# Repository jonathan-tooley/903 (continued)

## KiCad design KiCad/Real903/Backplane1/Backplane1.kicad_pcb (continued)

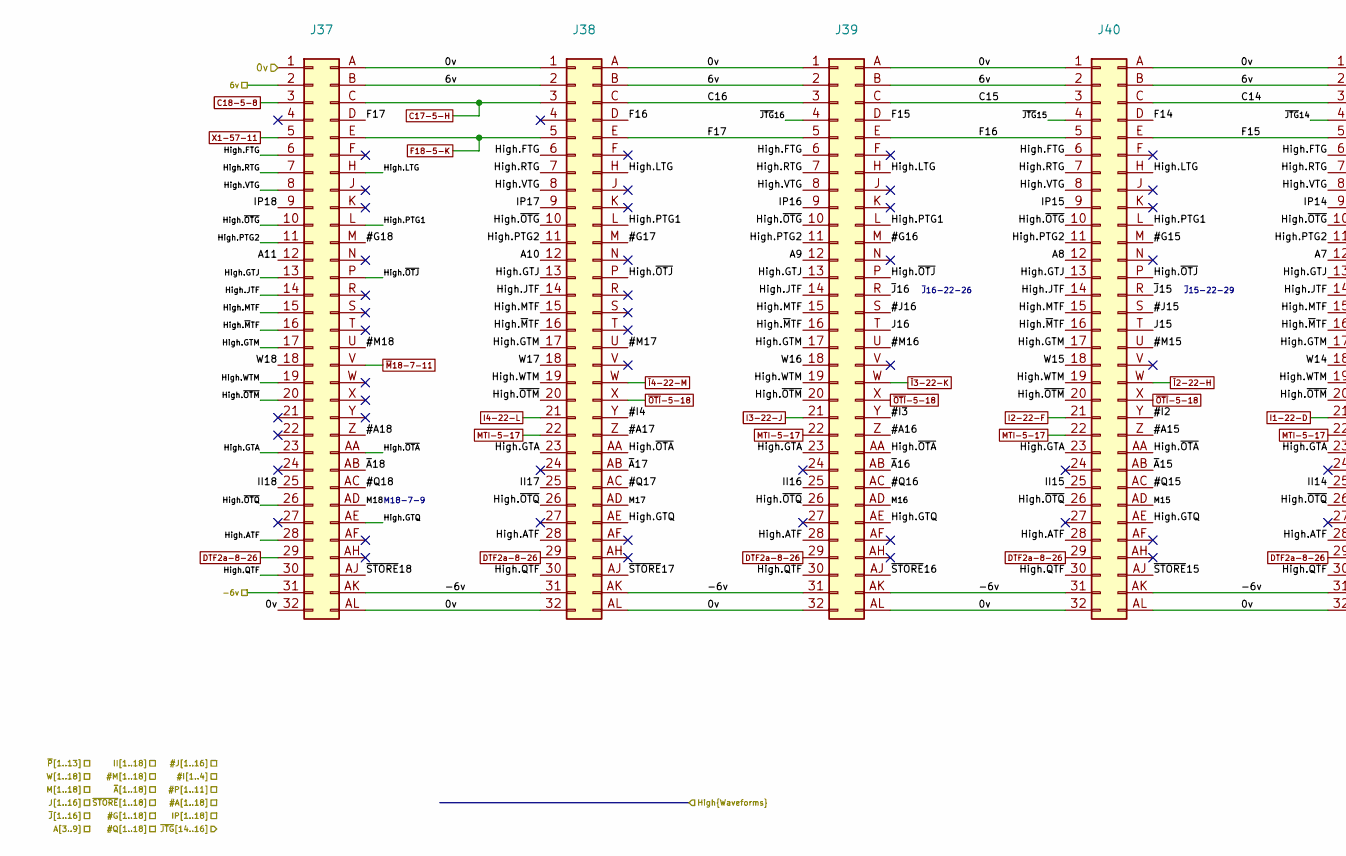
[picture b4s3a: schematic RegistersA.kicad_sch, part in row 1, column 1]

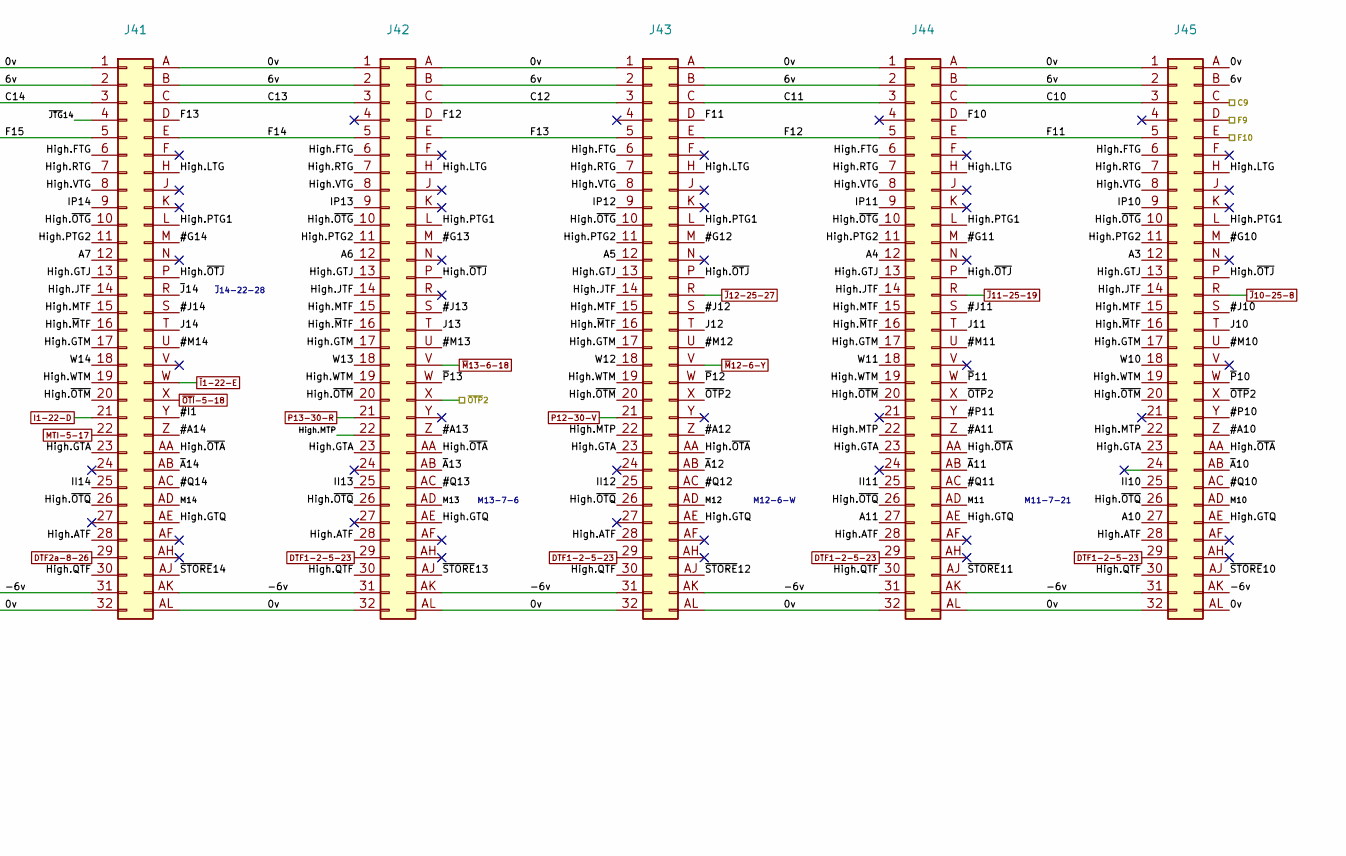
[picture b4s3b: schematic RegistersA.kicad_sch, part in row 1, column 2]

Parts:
J37, J38, J39, J40, J41, J42, J43, J44, J45: DIN41612_B_2x32_Vertical

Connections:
0v: J37.1, J37.32, J37.A, J37.AL, J38.1, J38.32, J38.A, J38.AL, J39.1, J39.32, J39.A, J39.AL, J40.1, J40.32, J40.A, J40.AL, J41.1, J41.32, J41.A, J41.AL, J42.1, J42.32, J42.A, J42.AL, J43.1, J43.32, J43.A, J43.AL, J44.1, J44.32, J44.A, J44.AL, J45.1, J45.32, J45.A, J45.AL; also elsewhere on the board
6v: J37.2, J37.B, J38.2, J38.B, J39.2, J39.B, J40.2, J40.B, J41.2, J41.B, J42.2, J42.B, J43.2, J43.B, J44.2, J44.B, J45.2, J45.B; also elsewhere on the board
#A10: J45.Z; also elsewhere on the board
#A11: J44.Z; also elsewhere on the board
#A12: J43.Z; also elsewhere on the board
#A13: J42.Z; also elsewhere on the board
#A14: J41.Z; also elsewhere on the board
#A15: J40.Z; also elsewhere on the board
#A16: J39.Z; also elsewhere on the board
#A17: J38.Z; also elsewhere on the board
#A18: J37.Z; also elsewhere on the board
#G10: J45.M; also elsewhere on the board
#G11: J44.M; also elsewhere on the board
#G12: J43.M; also elsewhere on the board
#G13: J42.M; also elsewhere on the board
#G14: J41.M; also elsewhere on the board
#G15: J40.M; also elsewhere on the board
#G16: J39.M; also elsewhere on the board
#G17: J38.M; also elsewhere on the board
#G18: J37.M; also elsewhere on the board
#I1: J41.Y; also elsewhere on the board
#I2: J40.Y; also elsewhere on the board
#I3: J39.Y; also elsewhere on the board
#I4: J38.Y; also elsewhere on the board
#J10: J45.S; also elsewhere on the board
#J11: J44.S; also elsewhere on the board
#J12: J43.S; also elsewhere on the board
#J13: J42.S; also elsewhere on the board
#J14: J41.S; also elsewhere on the board
#J15: J40.S; also elsewhere on the board
#J16: J39.S; also elsewhere on the board
#M10: J45.U; also elsewhere on the board
#M11: J44.U; also elsewhere on the board
#M12: J43.U; also elsewhere on the board
#M13: J42.U; also elsewhere on the board
#M14: J41.U; also elsewhere on the board
#M15: J40.U; also elsewhere on the board
#M16: J39.U; also elsewhere on the board
#M17: J38.U; also elsewhere on the board
#M18: J37.U; also elsewhere on the board
#P10: J45.Y; also elsewhere on the board
#P11: J44.Y; also elsewhere on the board
#Q10: J45.AC; also elsewhere on the board
#Q11: J44.AC; also elsewhere on the board
#Q12: J43.AC; also elsewhere on the board
#Q13: J42.AC; also elsewhere on the board
#Q14: J41.AC; also elsewhere on the board
#Q15: J40.AC; also elsewhere on the board
#Q16: J39.AC; also elsewhere on the board
#Q17: J38.AC; also elsewhere on the board
#Q18: J37.AC; also elsewhere on the board
/Connections/~J14: J41.R; also elsewhere on the board
/Connections/~J15: J40.R; also elsewhere on the board
/Connections/~J16: J39.R; also elsewhere on the board
/RegistersA/A3: J45.12; also elsewhere on the board
/RegistersA/A4: J44.12; also elsewhere on the board
/RegistersA/A5: J43.12; also elsewhere on the board
/RegistersA/A6: J42.12; also elsewhere on the board
/RegistersA/A7: J41.12; also elsewhere on the board
/RegistersA/A8: J40.12; also elsewhere on the board
/RegistersA/A9: J39.12; also elsewhere on the board
/RegistersA/A10: J38.12, J45.27
/RegistersA/A11: J37.12, J44.27
/RegistersA/ATF2: J37.28, J38.28, J39.28, J40.28, J41.28, J42.28, J43.28, J44.28, J45.28; also elsewhere on the board
/RegistersA/C9: J45.C; also elsewhere on the board
/RegistersA/C10: J44.C, J45.3
/RegistersA/C11: J43.C, J44.3
/RegistersA/C12: J42.C, J43.3
/RegistersA/C13: J41.C, J42.3
/RegistersA/C14: J40.C, J41.3
/RegistersA/C15: J39.C, J40.3
/RegistersA/C16: J38.C, J39.3
/RegistersA/F10: J44.D, J45.E; also elsewhere on the board
/RegistersA/F11: J43.D, J44.E, J45.5
/RegistersA/F12: J42.D, J43.E, J44.5
/RegistersA/F13: J41.D, J42.E, J43.5
/RegistersA/F14: J40.D, J41.E, J42.5
/RegistersA/F15: J39.D, J40.E, J41.5
/RegistersA/F16: J38.D, J39.E, J40.5
/RegistersA/F17: J37.D, J38.E, J39.5
/RegistersA/FTG2: J37.6, J38.6, J39.6, J40.6, J41.6, J42.6, J43.6, J44.6, J45.6; also elsewhere on the board
/RegistersA/GTA2: J37.23, J38.23, J39.23, J40.23, J41.23, J42.23, J43.23, J44.23, J45.23; also elsewhere on the board
/RegistersA/GTJ2: J37.13, J38.13, J39.13, J40.13, J41.13, J42.13, J43.13, J44.13, J45.13; also elsewhere on the board
/RegistersA/GTM2: J37.17, J38.17, J39.17, J40.17, J41.17, J42.17, J43.17, J44.17, J45.17; also elsewhere on the board
/RegistersA/GTQ2: J37.AE, J38.AE, J39.AE, J40.AE, J41.AE, J42.AE, J43.AE, J44.AE, J45.AE; also elsewhere on the board
/RegistersA/JTF2: J37.14, J38.14, J39.14, J40.14, J41.14, J42.14, J43.14, J44.14, J45.14; also elsewhere on the board
/RegistersA/LTG2: J37.H, J38.H, J39.H, J40.H, J41.H, J42.H, J43.H, J44.H, J45.H; also elsewhere on the board
/RegistersA/MTF2: J37.15, J38.15, J39.15, J40.15, J41.15, J42.15, J43.15, J44.15, J45.15; also elsewhere on the board
/RegistersA/MTP2: J42.22, J43.22, J44.22, J45.22; also elsewhere on the board
/RegistersA/PTG1-2: J37.L, J38.L, J39.L, J40.L, J41.L, J42.L, J43.L, J44.L, J45.L; also elsewhere on the board
/RegistersA/PTG2-2: J37.11, J38.11, J39.11, J40.11, J41.11, J42.11, J43.11, J44.11, J45.11; also elsewhere on the board
/RegistersA/QTF2: J37.30, J38.30, J39.30, J40.30, J41.30, J42.30, J43.30, J44.30, J45.30; also elsewhere on the board
/RegistersA/RTG2: J37.7, J38.7, J39.7, J40.7, J41.7, J42.7, J43.7, J44.7, J45.7; also elsewhere on the board
/RegistersA/VTG2: J37.8, J38.8, J39.8, J40.8, J41.8, J42.8, J43.8, J44.8, J45.8; also elsewhere on the board
/RegistersA/WTM2: J37.19, J38.19, J39.19, J40.19, J41.19, J42.19, J43.19, J44.19, J45.19; also elsewhere on the board
/RegistersA/~JTG14: J41.4; also elsewhere on the board
/RegistersA/~JTG15: J40.4; also elsewhere on the board
/RegistersA/~JTG16: J39.4; also elsewhere on the board
/RegistersA/~MTF2: J37.16, J38.16, J39.16, J40.16, J41.16, J42.16, J43.16, J44.16, J45.16; also elsewhere on the board
/RegistersA/~OTA2: J37.AA, J38.AA, J39.AA, J40.AA, J41.AA, J42.AA, J43.AA, J44.AA, J45.AA; also elsewhere on the board
/RegistersA/~OTG2: J37.10, J38.10, J39.10, J40.10, J41.10, J42.10, J43.10, J44.10, J45.10; also elsewhere on the board
/RegistersA/~OTJ2: J37.P, J38.P, J39.P, J40.P, J41.P, J42.P, J43.P, J44.P, J45.P; also elsewhere on the board
/RegistersA/~OTM2: J37.20, J38.20, J39.20, J40.20, J41.20, J42.20, J43.20, J44.20, J45.20; also elsewhere on the board
/RegistersA/~OTP2: J42.X, J43.X, J44.X, J45.X; also elsewhere on the board
/RegistersA/~OTQ2: J37.26, J38.26, J39.26, J40.26, J41.26, J42.26, J43.26, J44.26, J45.26; also elsewhere on the board
/RegistersB/F9: J45.D; also elsewhere on the board
C17-5-H: J37.C, J38.3; also elsewhere on the board
C18-5-8: J37.3; also elsewhere on the board
DTF1-2-5-23: J42.29, J43.29, J44.29, J45.29; also elsewhere on the board
DTF2a-8-26: J37.29, J38.29, J39.29, J40.29, J41.29; also elsewhere on the board
F18-5-K: J37.E, J38.5; also elsewhere on the board
I1-22-D: J41.21; also elsewhere on the board
I2-22-F: J40.21; also elsewhere on the board
I3-22-J: J39.21; also elsewhere on the board
I4-22-L: J38.21; also elsewhere on the board
II10: J45.25; also elsewhere on the board
II11: J44.25; also elsewhere on the board
II12: J43.25; also elsewhere on the board
II13: J42.25; also elsewhere on the board
II14: J41.25; also elsewhere on the board
II15: J40.25; also elsewhere on the board
II16: J39.25; also elsewhere on the board
II17: J38.25; also elsewhere on the board
II18: J37.25; also elsewhere on the board
IP10: J45.9; also elsewhere on the board
IP11: J44.9; also elsewhere on the board
IP12: J43.9; also elsewhere on the board
IP13: J42.9; also elsewhere on the board
IP14: J41.9; also elsewhere on the board
IP15: J40.9; also elsewhere on the board
IP16: J39.9; also elsewhere on the board
IP17: J38.9; also elsewhere on the board
IP18: J37.9; also elsewhere on the board
J10: J45.T; also elsewhere on the board
J11: J44.T; also elsewhere on the board
J12: J43.T; also elsewhere on the board
J13: J42.T; also elsewhere on the board
J14: J41.T; also elsewhere on the board
J15: J40.T; also elsewhere on the board
J16: J39.T; also elsewhere on the board
M10: J45.AD; also elsewhere on the board
M11: J44.AD; also elsewhere on the board
M12: J43.AD; also elsewhere on the board
M13: J42.AD; also elsewhere on the board
M14: J41.AD; also elsewhere on the board
M15: J40.AD; also elsewhere on the board
M16: J39.AD; also elsewhere on the board
M17: J38.AD; also elsewhere on the board
M18: J37.AD; also elsewhere on the board
MTI-5-17: J38.22, J39.22, J40.22, J41.22; also elsewhere on the board
Neg6v: J37.31, J37.AK, J38.31, J38.AK, J39.31, J39.AK, J40.31, J40.AK, J41.31, J41.AK, J42.31, J42.AK, J43.31, J43.AK, J44.31, J44.AK, J45.31, J45.AK; also elsewhere on the board
P12-30-V: J43.21; also elsewhere on the board
P13-30-R: J42.21; also elsewhere on the board
W10: J45.18; also elsewhere on the board
W11: J44.18; also elsewhere on the board
W12: J43.18; also elsewhere on the board
W13: J42.18; also elsewhere on the board
W14: J41.18; also elsewhere on the board
W15: J40.18; also elsewhere on the board
W16: J39.18; also elsewhere on the board
W17: J38.18; also elsewhere on the board
W18: J37.18; also elsewhere on the board
X1-57-11: J37.5; also elsewhere on the board
~A10: J45.AB; also elsewhere on the board
~A11: J44.AB; also elsewhere on the board
~A12: J43.AB; also elsewhere on the board
~A13: J42.AB; also elsewhere on the board
~A14: J41.AB; also elsewhere on the board
~A15: J40.AB; also elsewhere on the board
~A16: J39.AB; also elsewhere on the board
~A17: J38.AB; also elsewhere on the board
~A18: J37.AB; also elsewhere on the board
~I1-22-E: J41.W; also elsewhere on the board
~I2-22-H: J40.W; also elsewhere on the board
~I3-22-K: J39.W; also elsewhere on the board
~I4-22-M: J38.W; also elsewhere on the board
~J10-25-8: J45.R; also elsewhere on the board
~J11-25-19: J44.R; also elsewhere on the board
~J12-25-27: J43.R; also elsewhere on the board
~M12-6-Y: J43.V; also elsewhere on the board
~M13-6-18: J42.V; also elsewhere on the board
~M18-7-11: J37.V; also elsewhere on the board
~OTI-5-18: J38.X, J39.X, J40.X, J41.X; also elsewhere on the board
~P10: J45.W; also elsewhere on the board
~P11: J44.W; also elsewhere on the board
~P12: J43.W; also elsewhere on the board
~P13: J42.W; also elsewhere on the board
~STORE10: J45.AJ; also elsewhere on the board
~STORE11: J44.AJ; also elsewhere on the board
~STORE12: J43.AJ; also elsewhere on the board
~STORE13: J42.AJ; also elsewhere on the board
~STORE14: J41.AJ; also elsewhere on the board
~STORE15: J40.AJ; also elsewhere on the board
~STORE16: J39.AJ; also elsewhere on the board
~STORE17: J38.AJ; also elsewhere on the board
~STORE18: J37.AJ; also elsewhere on the board

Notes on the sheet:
~{J}14-22-28
~{J}15-22-29
M18-7-9
M13-7-6
M12-6-W
M11-7-21
~{J}16-22-26

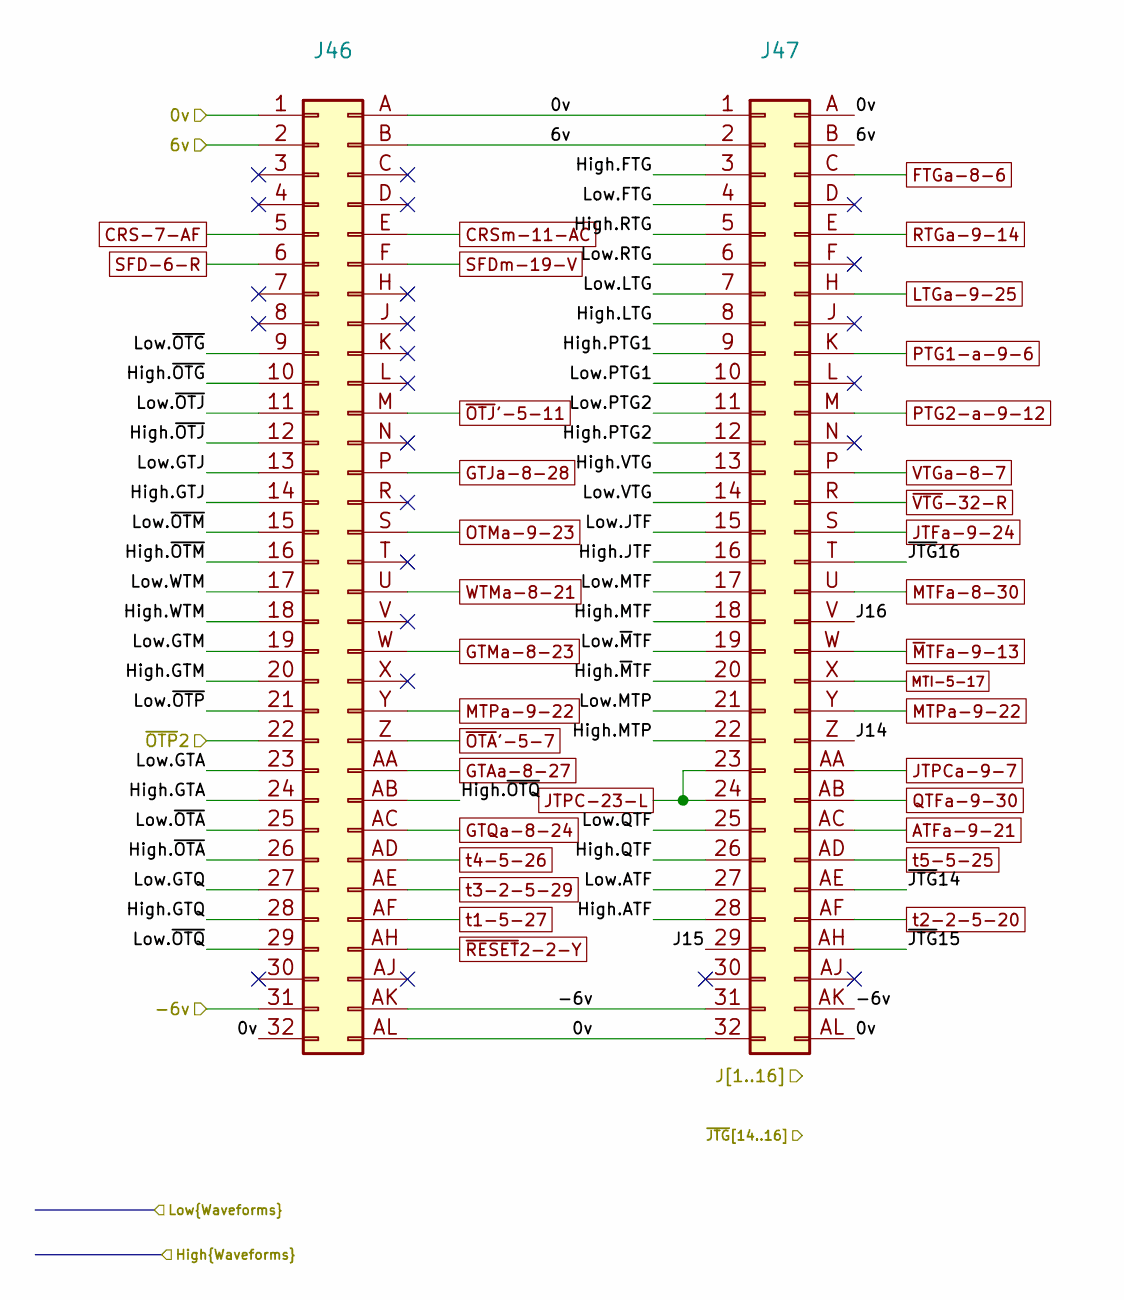
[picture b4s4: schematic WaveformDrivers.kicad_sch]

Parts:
J46, J47: DIN41612_B_2x32_Vertical

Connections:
0v: J46.1, J46.32, J46.A, J46.AL, J47.1, J47.32, J47.A, J47.AL; also elsewhere on the board
6v: J46.2, J46.B, J47.2, J47.B; also elsewhere on the board
/Low.FTG: J47.4; also elsewhere on the board
/Low.GTA: J46.23; also elsewhere on the board
/Low.GTJ: J46.13; also elsewhere on the board
/Low.GTM: J46.19; also elsewhere on the board
/Low.JTF: J47.15; also elsewhere on the board
/Low.LTG: J47.7; also elsewhere on the board
/Low.MTF: J47.17; also elsewhere on the board
/Low.MTP: J47.21; also elsewhere on the board
/Low.PTG1: J47.10; also elsewhere on the board
/Low.PTG2: J47.11; also elsewhere on the board
/Low.RTG: J47.6; also elsewhere on the board
/Low.VTG: J47.14; also elsewhere on the board
/Low.WTM: J46.17; also elsewhere on the board
/Low.~OTG: J46.9; also elsewhere on the board
/Low.~OTJ: J46.11; also elsewhere on the board
/Low.~OTM: J46.15; also elsewhere on the board
/RegistersA/ATF2: J47.28; also elsewhere on the board
/RegistersA/FTG2: J47.3; also elsewhere on the board
/RegistersA/GTA2: J46.24; also elsewhere on the board
/RegistersA/GTJ2: J46.14; also elsewhere on the board
/RegistersA/GTM2: J46.20; also elsewhere on the board
/RegistersA/GTQ2: J46.28; also elsewhere on the board
/RegistersA/JTF2: J47.16; also elsewhere on the board
/RegistersA/LTG2: J47.8; also elsewhere on the board
/RegistersA/MTF2: J47.18; also elsewhere on the board
/RegistersA/MTP2: J47.22; also elsewhere on the board
/RegistersA/PTG1-2: J47.9; also elsewhere on the board
/RegistersA/PTG2-2: J47.12; also elsewhere on the board
/RegistersA/QTF2: J47.26; also elsewhere on the board
/RegistersA/RTG2: J47.5; also elsewhere on the board
/RegistersA/VTG2: J47.13; also elsewhere on the board
/RegistersA/WTM2: J46.18; also elsewhere on the board
/RegistersA/~JTG14: J47.AE; also elsewhere on the board
/RegistersA/~JTG15: J47.AH; also elsewhere on the board
/RegistersA/~JTG16: J47.T; also elsewhere on the board
/RegistersA/~MTF2: J47.19; also elsewhere on the board
/RegistersA/~OTA2: J46.26; also elsewhere on the board
/RegistersA/~OTG2: J46.10; also elsewhere on the board
/RegistersA/~OTJ2: J46.12; also elsewhere on the board
/RegistersA/~OTM2: J46.16; also elsewhere on the board
/RegistersA/~OTP2: J46.22; also elsewhere on the board
/RegistersA/~OTQ2: J46.AB; also elsewhere on the board
/RegistersB/ATF1: J47.27; also elsewhere on the board
/RegistersB/GTQ1: J46.27; also elsewhere on the board
/RegistersB/QTF1: J47.25; also elsewhere on the board
/RegistersB/~MTF1: J47.20; also elsewhere on the board
/RegistersB/~OTA1: J46.25; also elsewhere on the board
/RegistersB/~OTP1: J46.21; also elsewhere on the board
/RegistersB/~OTQ1: J46.29; also elsewhere on the board
ATFa-9-21: J47.AC; also elsewhere on the board
CRS-7-AF: J46.5; also elsewhere on the board
CRSm-11-AC: J46.E; also elsewhere on the board
FTGa-8-6: J47.C; also elsewhere on the board
GTAa-8-27: J46.AA; also elsewhere on the board
GTJa-8-28: J46.P; also elsewhere on the board
GTMa-8-23: J46.W; also elsewhere on the board
GTQa-8-24: J46.AC; also elsewhere on the board
J14: J47.Z; also elsewhere on the board
J15: J47.29; also elsewhere on the board
J16: J47.V; also elsewhere on the board
JTFa-9-24: J47.S; also elsewhere on the board
JTPC-23-L: J47.23, J47.24; also elsewhere on the board
JTPCa-9-7: J47.AA; also elsewhere on the board
LTGa-9-25: J47.H; also elsewhere on the board
MTFa-8-30: J47.U; also elsewhere on the board
MTI-5-17: J47.X; also elsewhere on the board
MTPa-9-22: J46.Y, J47.Y; also elsewhere on the board
Neg6v: J46.31, J46.AK, J47.31, J47.AK; also elsewhere on the board
OTMa-9-23: J46.S; also elsewhere on the board
PTG1-a-9-6: J47.K; also elsewhere on the board
PTG2-a-9-12: J47.M; also elsewhere on the board
QTFa-9-30: J47.AB; also elsewhere on the board
RTGa-9-14: J47.E; also elsewhere on the board
SFD-6-R: J46.6; also elsewhere on the board
SFDm-19-V: J46.F; also elsewhere on the board
VTGa-8-7: J47.P; also elsewhere on the board
WTMa-8-21: J46.U; also elsewhere on the board
t1-5-27: J46.AF; also elsewhere on the board
t2-2-5-20: J47.AF; also elsewhere on the board
t3-2-5-29: J46.AE; also elsewhere on the board
t4-5-26: J46.AD; also elsewhere on the board
t5-5-25: J47.AD; also elsewhere on the board
~MTFa-9-13: J47.W; also elsewhere on the board
~OTA'-5-7: J46.Z; also elsewhere on the board
~OTJ'-5-11: J46.M; also elsewhere on the board
~RESET2-2-Y: J46.AH; also elsewhere on the board
~VTG-32-R: J47.R; also elsewhere on the board
